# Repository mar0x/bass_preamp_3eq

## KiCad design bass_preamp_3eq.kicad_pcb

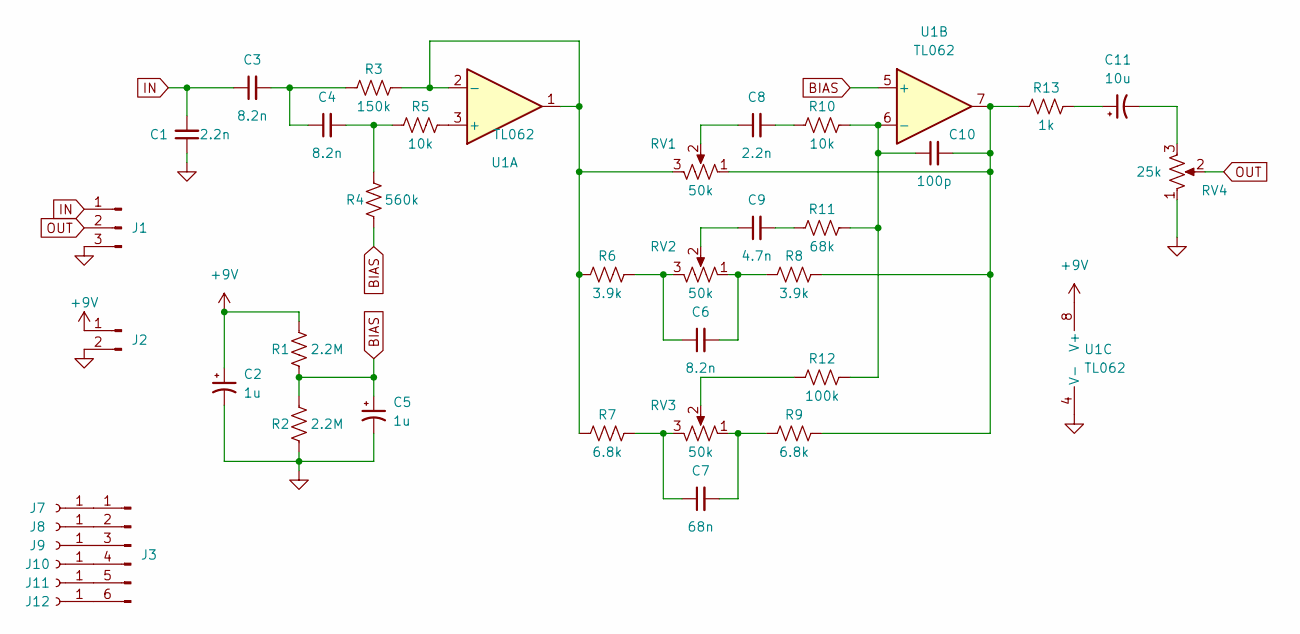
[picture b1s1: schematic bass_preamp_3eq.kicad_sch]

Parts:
C1, C8: 2.2n; C_Rect_L7.2mm_W3.0mm_P5.00mm_FKS2_FKP2_MKS2_MKP2
C2, C5: 1u; CP_Radial_D5.0mm_P2.50mm
C3, C4, C6: 8.2n; C_Rect_L7.2mm_W3.0mm_P5.00mm_FKS2_FKP2_MKS2_MKP2
C7: 68n; C_Rect_L7.2mm_W3.0mm_P5.00mm_FKS2_FKP2_MKS2_MKP2
C9: 4.7n; C_Rect_L7.2mm_W3.0mm_P5.00mm_FKS2_FKP2_MKS2_MKP2
C10: 100p; C_Disc_D6.0mm_W2.5mm_P5.00mm
C11: 10u; CP_Radial_D5.0mm_P2.50mm
J1: Conn_01x03_Male; JST_PH_B3B-PH-K_1x03_P2.00mm_Vertical
J2: Conn_01x02_Male; JST_PH_B2B-PH-K_1x02_P2.00mm_Vertical
J3: Conn_01x06_Male; JST_PH_B6B-PH-K_1x06_P2.00mm_Vertical
J7, J8, J9, J10, J11, J12: Conn_01x01_Female; PinSocket_1x01_P2.54mm_Vertical
R1, R2: 2.2M; R_1206_3216Metric
R3: 150k; R_1206_3216Metric
R4: 560k; R_1206_3216Metric
R5, R10: 10k; R_1206_3216Metric
R6, R8: 3.9k; R_1206_3216Metric
R7, R9: 6.8k; R_1206_3216Metric
R11: 68k; R_1206_3216Metric
R12: 100k; R_1206_3216Metric
R13: 1k; R_1206_3216Metric
RV1, RV2, RV3: 50k; Potentiometer_Piher_T-16L_Single_Vertical_Hole
RV4: 25k; Potentiometer_Piher_T-16L_Single_Vertical_Hole
U1: TL062; DIP-8_W7.62mm

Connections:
+9V: C2.1, J2.1, R1.2, U1.8 (V+)
BIAS: C5.1, R1.1, R2.2, R4.1, U1.5 (+)
GND: C1.1, C2.2, C5.2, J1.3, J2.2, R2.1, RV4.1, U1.4 (V-)
IN: C1.2, C3.1, J1.1
unnamed: C3.2, C4.1, R3.1
unnamed: C4.2, R4.2, R5.1
unnamed: C6.1, R6.2, RV2.3
unnamed: C6.2, R8.1, RV2.1
unnamed: C7.1, R7.2, RV3.3
unnamed: C7.2, R9.1, RV3.1
unnamed: C8.1, RV1.2
unnamed: C8.2, R10.1
unnamed: C9.1, RV2.2
unnamed: C9.2, R11.1
unnamed: C11.1, R13.2
unnamed: C11.2, RV4.3
unnamed: J3.1, J7.1
unnamed: J3.2, J8.1
unnamed: J3.3, J9.1
unnamed: J3.4, J10.1
unnamed: J3.5, J11.1
unnamed: J3.6, J12.1
unnamed: R3.2, R6.1, R7.1, RV1.3, U1.1, U1.2 (-)
unnamed: R5.2, U1.3 (+)
unnamed: C10.1, R10.2, R11.2, R12.2, U1.6 (-)
unnamed: R12.1, RV3.2
unnamed: C10.2, R8.2, R9.2, R13.1, RV1.1, U1.7
OUT: J1.2, RV4.2

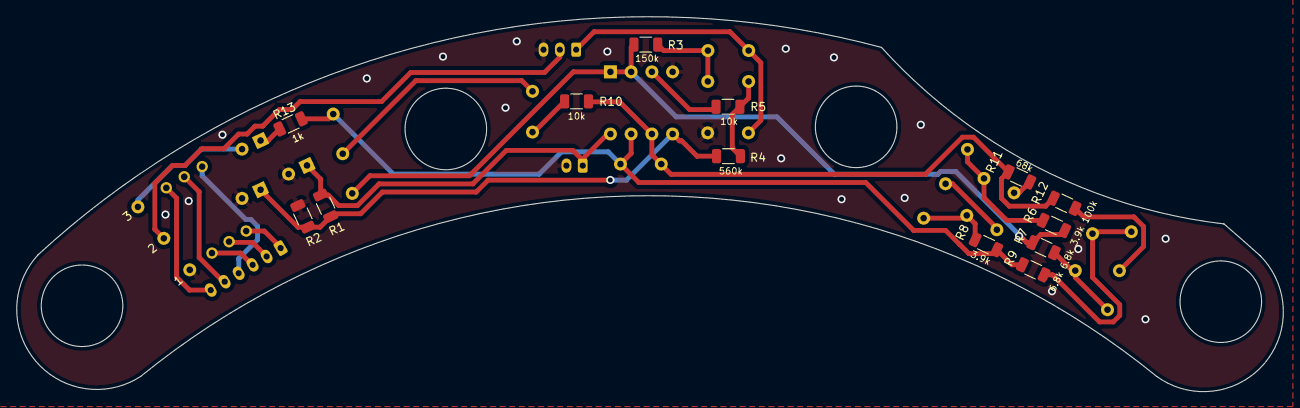
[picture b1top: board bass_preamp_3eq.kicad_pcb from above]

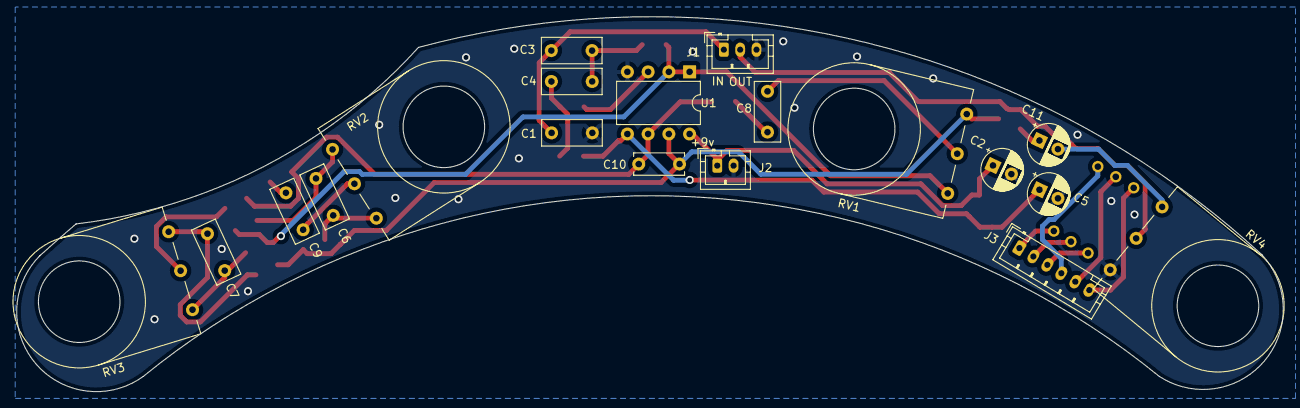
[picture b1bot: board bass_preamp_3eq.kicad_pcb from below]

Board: 2 copper layers, 155.3 x 46.0 mm, 38 parts (19 on the bottom side), 28 nets.

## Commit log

2023-02-13 Moving values on the back
2023-02-14 Manual fixes after rounding tracks
2023-02-14 Original schematic and drawing
